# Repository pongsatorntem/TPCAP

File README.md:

TPCAP_autofeed_raspi --> can use in reality 100% detection at Export

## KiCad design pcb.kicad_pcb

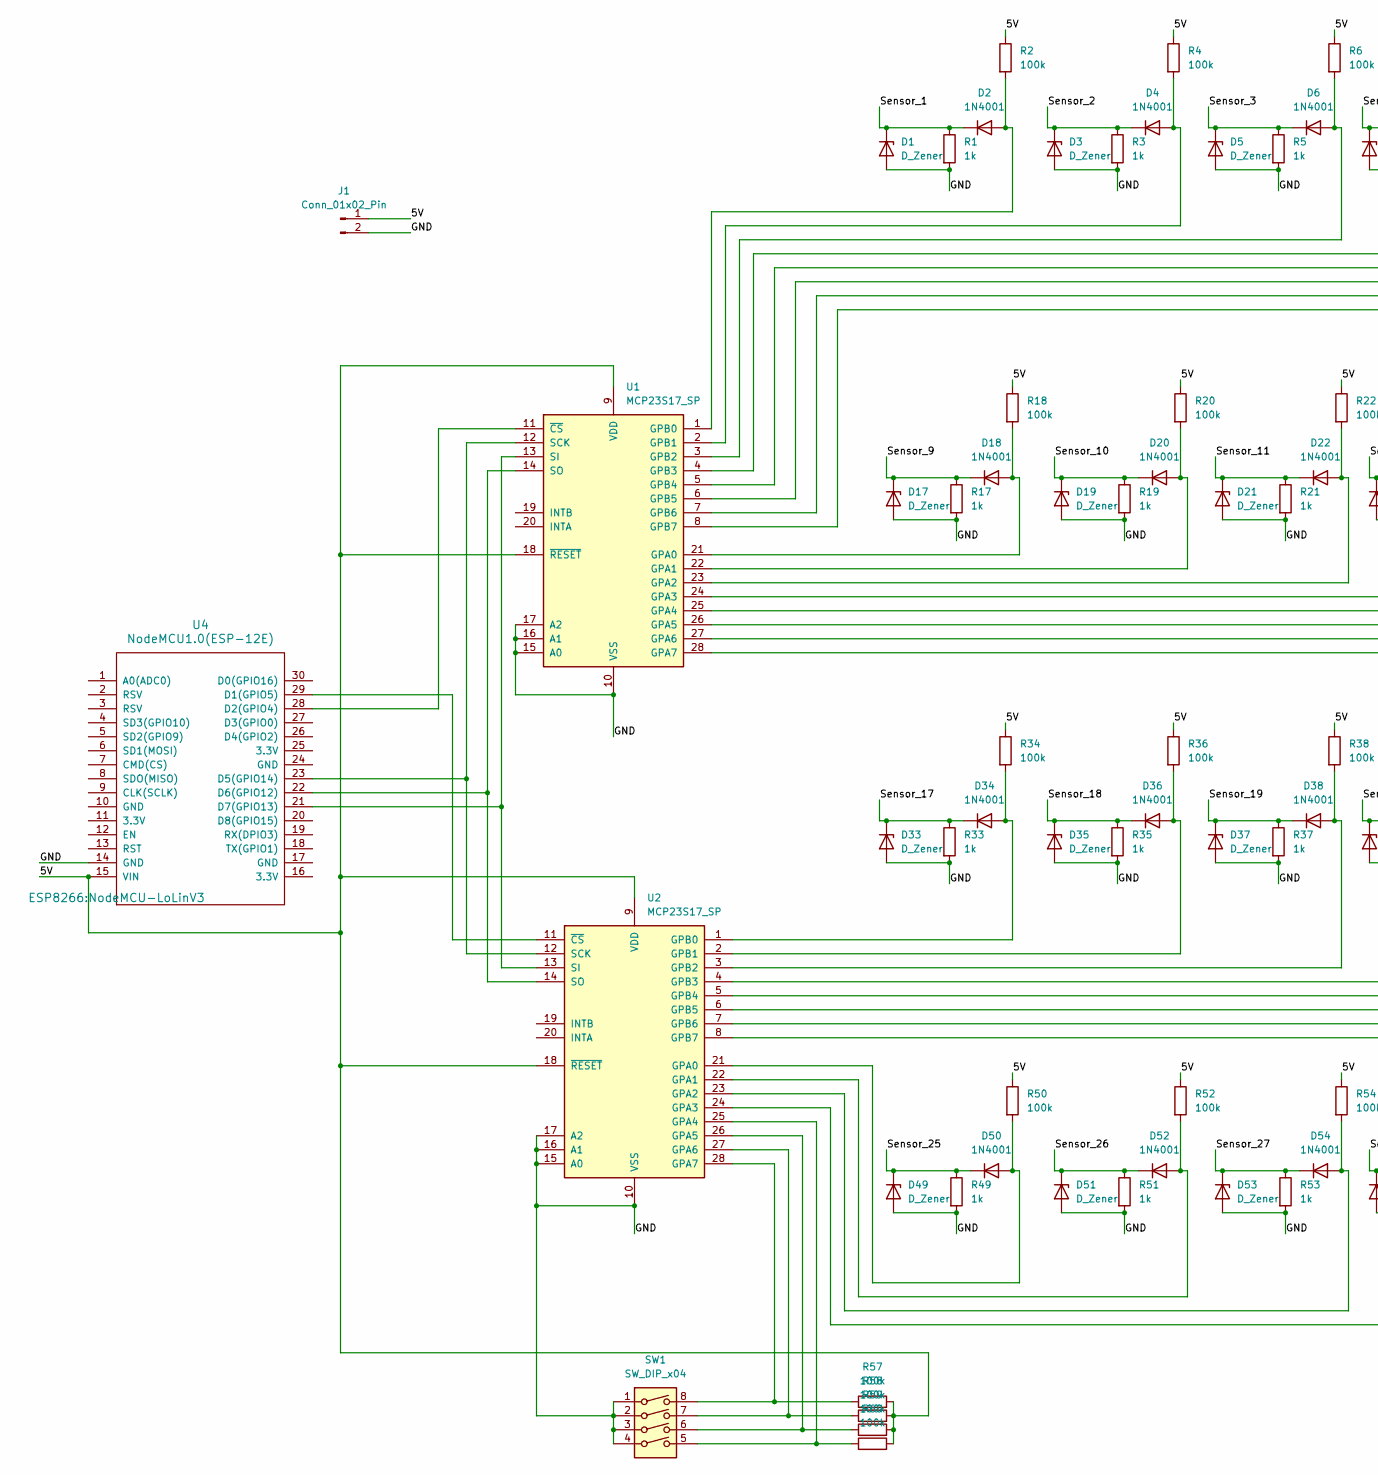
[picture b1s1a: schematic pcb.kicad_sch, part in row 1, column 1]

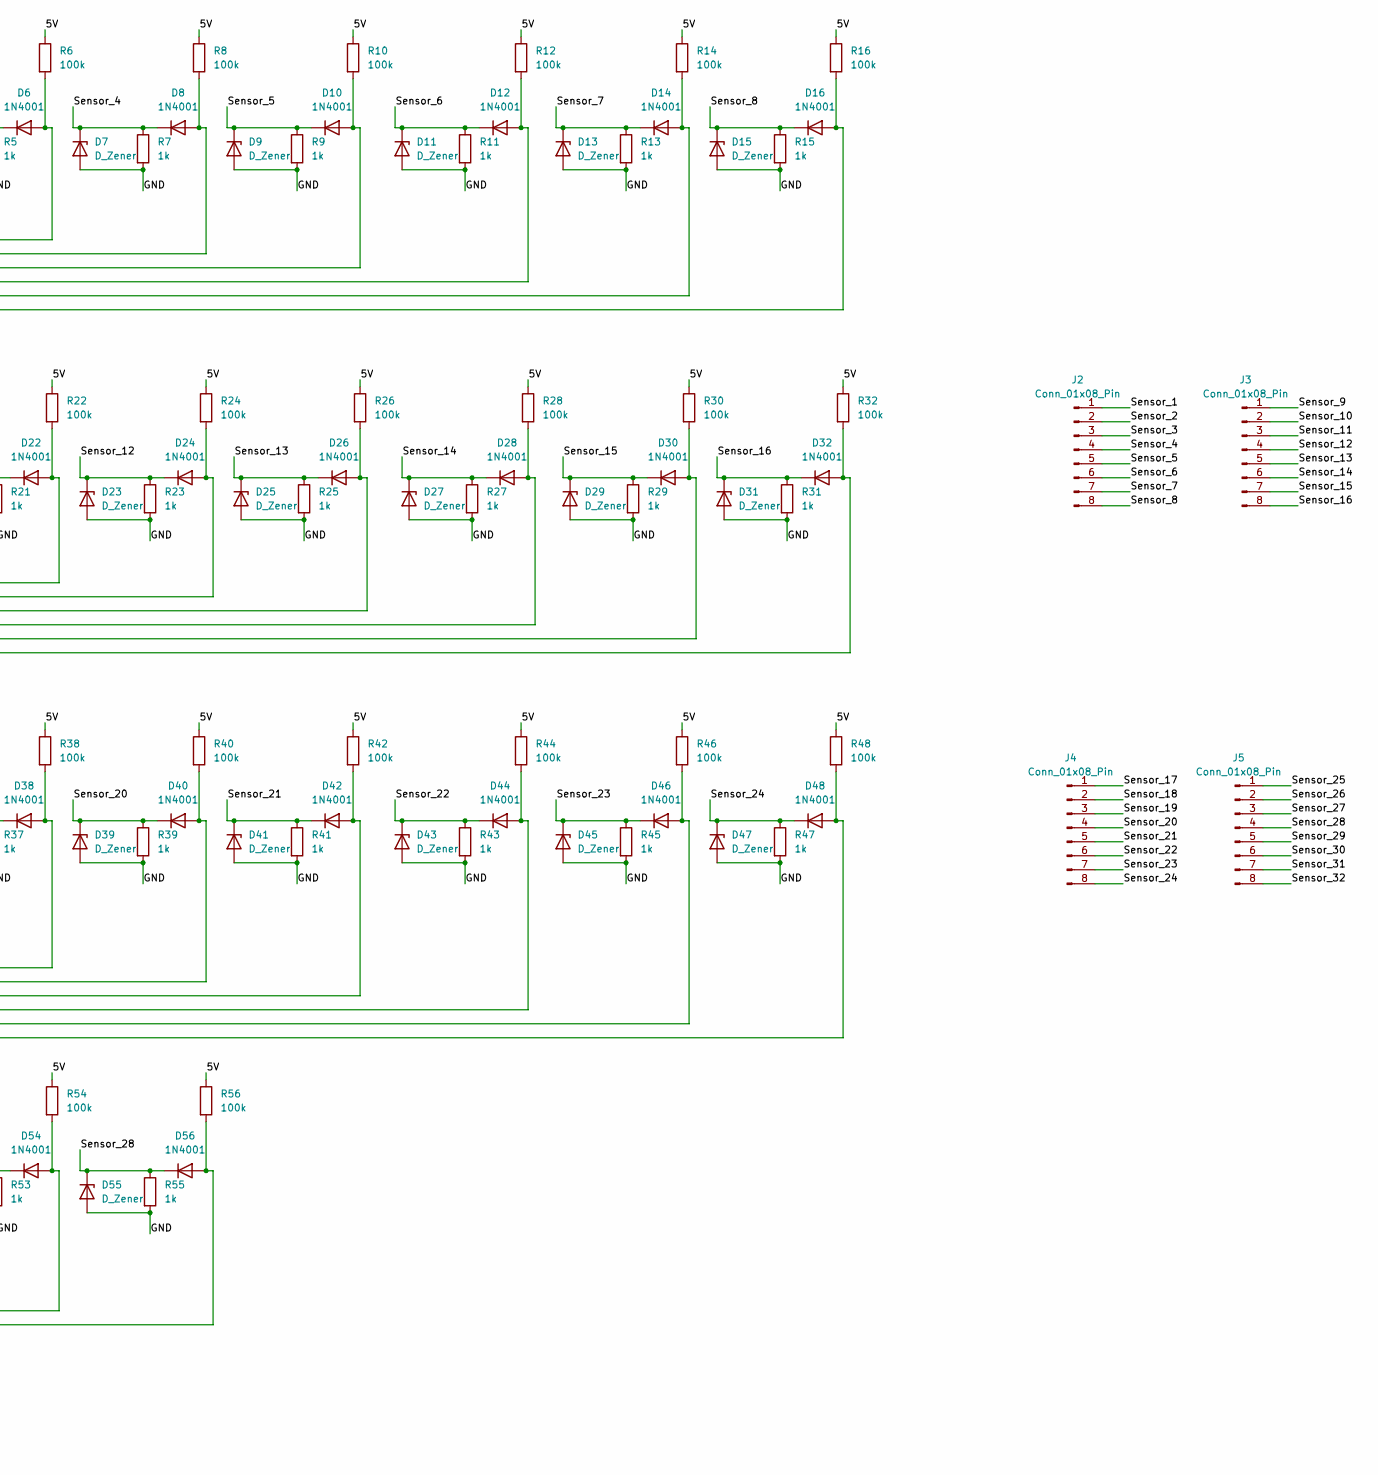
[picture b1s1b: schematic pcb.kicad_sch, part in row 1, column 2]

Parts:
D1, D3, D5, D7, D9, D11, D13, D15, D17, D19, D21, D23, D25, D27, D29, D31, D33, D35, D37, D39, D41, D43, D45, D47, D49, D51, D53, D55: D_Zener; D_DO-41_SOD81_P10.16mm_Horizontal
D2, D4, D6, D8, D10, D12, D14, D16, D18, D20, D22, D24, D26, D28, D30, D32, D34, D36, D38, D40, D42, D44, D46, D48, D50, D52, D54, D56: 1N4001; D_DO-41_SOD81_P10.16mm_Horizontal
J1: Conn_01x02_Pin; TerminalBlock_Phoenix_PT-1,5-2-3.5-H_1x02_P3.50mm_Horizontal
J2, J3, J4, J5: Conn_01x08_Pin; TerminalBlock_Phoenix_PT-1,5-8-3.5-H_1x08_P3.50mm_Horizontal
R1, R3, R5, R7, R9, R11, R13, R15, R17, R19, R21, R23, R25, R27, R29, R31, R33, R35, R37, R39, R41, R43, R45, R47, R49, R51, R53, R55: 1k; R_Axial_DIN0411_L9.9mm_D3.6mm_P12.70mm_Horizontal
R2, R4, R6, R8, R10, R12, R14, R16, R18, R20, R22, R24, R26, R28, R30, R32, R34, R36, R38, R40, R42, R44, R46, R48, R50, R52, R54, R56, R57, R58, R59, R60: 100k; R_Axial_DIN0411_L9.9mm_D3.6mm_P12.70mm_Horizontal
SW1: SW_DIP_x04; DIP-8_W7.62mm_Socket
U1, U2: MCP23S17_SP; DIP-28_W7.62mm
U4: NodeMCU1.0(ESP-12E); NodeMCU-LoLinV3

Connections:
/5V: J1.1, R2.1, R4.1, R6.1, R8.1, R10.1, R12.1, R14.1, R16.1, R18.1, R20.1, R22.1, R24.1, R26.1, R28.1, R30.1, R32.1, R34.1, R36.1, R38.1, R40.1, R42.1, R44.1, R46.1, R48.1, R50.1, R52.1, R54.1, R56.1, R57.2, R58.2, R59.2, R60.2, U1.9 (VDD), U1.18 (~RESET), U2.9 (VDD), U2.18 (~RESET), U4.15 (VIN)
/GND: D1.2 (A), D3.2 (A), D5.2 (A), D7.2 (A), D9.2 (A), D11.2 (A), D13.2 (A), D15.2 (A), D17.2 (A), D19.2 (A), D21.2 (A), D23.2 (A), D25.2 (A), D27.2 (A), D29.2 (A), D31.2 (A), D33.2 (A), D35.2 (A), D37.2 (A), D39.2 (A), D41.2 (A), D43.2 (A), D45.2 (A), D47.2 (A), D49.2 (A), D51.2 (A), D53.2 (A), D55.2 (A), J1.2, R1.2, R3.2, R5.2, R7.2, R9.2, R11.2, R13.2, R15.2, R17.2, R19.2, R21.2, R23.2, R25.2, R27.2, R29.2, R31.2, R33.2, R35.2, R37.2, R39.2, R41.2, R43.2, R45.2, R47.2, R49.2, R51.2, R53.2, R55.2, SW1.1, SW1.2, SW1.3, SW1.4, U1.10 (VSS), U1.15 (A0), U1.16 (A1), U1.17 (A2), U2.10 (VSS), U2.15 (A0), U2.16 (A1), U2.17 (A2), U4.14 (GND)
/Sensor_1: D1.1 (K), D2.1 (K), J2.1, R1.1
/Sensor_2: D3.1 (K), D4.1 (K), J2.2, R3.1
/Sensor_3: D5.1 (K), D6.1 (K), J2.3, R5.1
/Sensor_4: D7.1 (K), D8.1 (K), J2.4, R7.1
/Sensor_5: D9.1 (K), D10.1 (K), J2.5, R9.1
/Sensor_6: D11.1 (K), D12.1 (K), J2.6, R11.1
/Sensor_7: D13.1 (K), D14.1 (K), J2.7, R13.1
/Sensor_8: D15.1 (K), D16.1 (K), J2.8, R15.1
/Sensor_9: D17.1 (K), D18.1 (K), J3.1, R17.1
/Sensor_10: D19.1 (K), D20.1 (K), J3.2, R19.1
/Sensor_11: D21.1 (K), D22.1 (K), J3.3, R21.1
/Sensor_12: D23.1 (K), D24.1 (K), J3.4, R23.1
/Sensor_13: D25.1 (K), D26.1 (K), J3.5, R25.1
/Sensor_14: D27.1 (K), D28.1 (K), J3.6, R27.1
/Sensor_15: D29.1 (K), D30.1 (K), J3.7, R29.1
/Sensor_16: D31.1 (K), D32.1 (K), J3.8, R31.1
/Sensor_17: D33.1 (K), D34.1 (K), J4.1, R33.1
/Sensor_18: D35.1 (K), D36.1 (K), J4.2, R35.1
/Sensor_19: D37.1 (K), D38.1 (K), J4.3, R37.1
/Sensor_20: D39.1 (K), D40.1 (K), J4.4, R39.1
/Sensor_21: D41.1 (K), D42.1 (K), J4.5, R41.1
/Sensor_22: D43.1 (K), D44.1 (K), J4.6, R43.1
/Sensor_23: D45.1 (K), D46.1 (K), J4.7, R45.1
/Sensor_24: D47.1 (K), D48.1 (K), J4.8, R47.1
/Sensor_25: D49.1 (K), D50.1 (K), J5.1, R49.1
/Sensor_26: D51.1 (K), D52.1 (K), J5.2, R51.1
/Sensor_27: D53.1 (K), D54.1 (K), J5.3, R53.1
/Sensor_28: D55.1 (K), D56.1 (K), J5.4, R55.1
/Sensor_29: J5.5
/Sensor_30: J5.6
/Sensor_31: J5.7
/Sensor_32: J5.8
unnamed: D2.2 (A), R2.2, U1.1 (GPB0)
unnamed: D4.2 (A), R4.2, U1.2 (GPB1)
unnamed: D6.2 (A), R6.2, U1.3 (GPB2)
unnamed: D8.2 (A), R8.2, U1.4 (GPB3)
unnamed: D10.2 (A), R10.2, U1.5 (GPB4)
unnamed: D12.2 (A), R12.2, U1.6 (GPB5)
unnamed: D14.2 (A), R14.2, U1.7 (GPB6)
unnamed: D16.2 (A), R16.2, U1.8 (GPB7)
unnamed: D18.2 (A), R18.2, U1.21 (GPA0)
unnamed: D20.2 (A), R20.2, U1.22 (GPA1)
unnamed: D22.2 (A), R22.2, U1.23 (GPA2)
unnamed: D24.2 (A), R24.2, U1.24 (GPA3)
unnamed: D26.2 (A), R26.2, U1.25 (GPA4)
unnamed: D28.2 (A), R28.2, U1.26 (GPA5)
unnamed: D30.2 (A), R30.2, U1.27 (GPA6)
unnamed: D32.2 (A), R32.2, U1.28 (GPA7)
unnamed: D34.2 (A), R34.2, U2.1 (GPB0)
unnamed: D36.2 (A), R36.2, U2.2 (GPB1)
unnamed: D38.2 (A), R38.2, U2.3 (GPB2)
unnamed: D40.2 (A), R40.2, U2.4 (GPB3)
unnamed: D42.2 (A), R42.2, U2.5 (GPB4)
unnamed: D44.2 (A), R44.2, U2.6 (GPB5)
unnamed: D46.2 (A), R46.2, U2.7 (GPB6)
unnamed: D48.2 (A), R48.2, U2.8 (GPB7)
unnamed: D50.2 (A), R50.2, U2.21 (GPA0)
unnamed: D52.2 (A), R52.2, U2.22 (GPA1)
unnamed: D54.2 (A), R54.2, U2.23 (GPA2)
unnamed: D56.2 (A), R56.2, U2.24 (GPA3)
unnamed: U1.12 (SCK), U2.12 (SCK), U4.23 (D5(GPIO14))
unnamed: U1.13 (SI), U2.13 (SI), U4.21 (D7(GPIO13))
unnamed: U1.14 (SO), U2.14 (SO), U4.22 (D6(GPIO12))
unnamed: U1.11 (~CS), U4.28 (D2(GPIO4))
unnamed: R60.1, SW1.5, U2.25 (GPA4)
unnamed: R59.1, SW1.6, U2.26 (GPA5)
unnamed: R58.1, SW1.7, U2.27 (GPA6)
unnamed: R57.1, SW1.8, U2.28 (GPA7)
unnamed: U2.11 (~CS), U4.29 (D1(GPIO5))

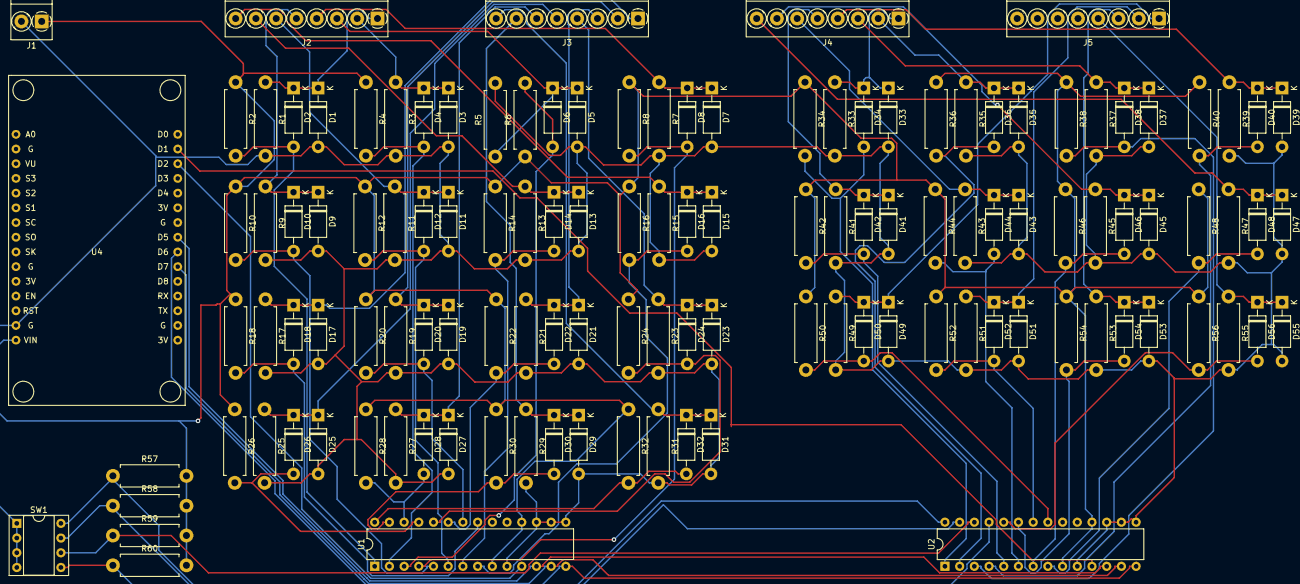
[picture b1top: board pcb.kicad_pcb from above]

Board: 2 copper layers, 125 parts (0 on the bottom side), 67 nets.

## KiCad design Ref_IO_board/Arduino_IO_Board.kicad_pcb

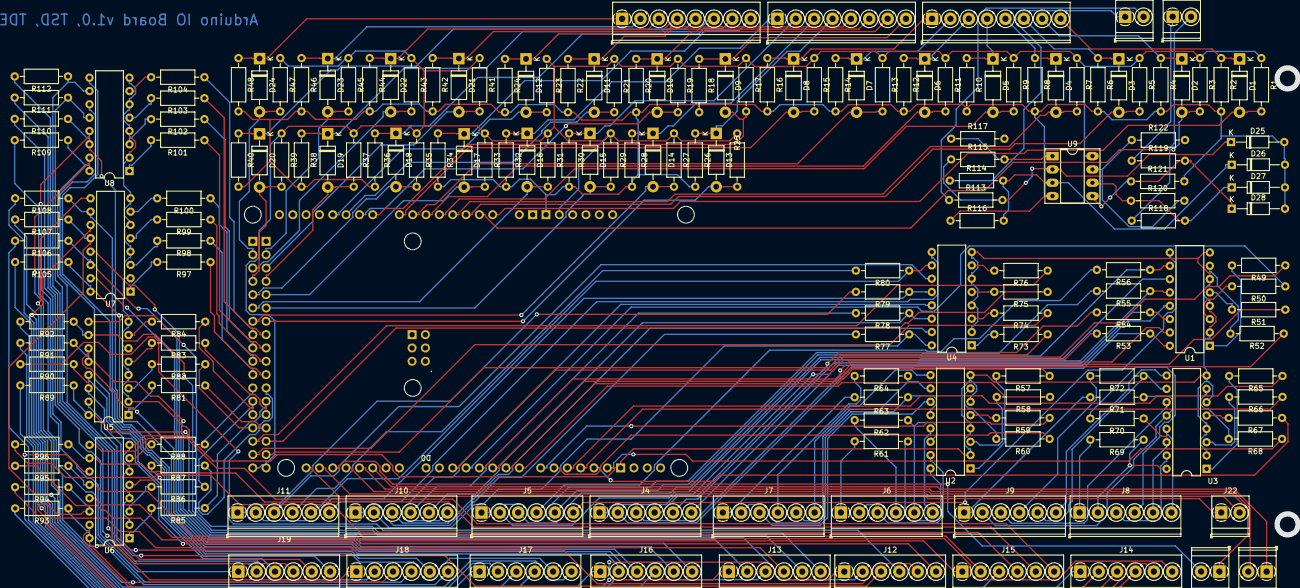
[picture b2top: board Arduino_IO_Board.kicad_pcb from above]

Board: 2 copper layers, 184 parts (0 on the bottom side), 227 nets.

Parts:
A1: Arduino_Mega2560_R3_Shield
D1, D2, D3, D4, D5, D6, D7, D8, D9, D10, D11, D12, D13, D14, D15, D16, D17, D18, D19, D20, D21, D22, D23, D24: 1N4002; D_DO-41_SOD81_P10.16mm_Horizontal
D25, D26, D27, D28: 1N53xxB; D_DO-35_SOD27_P10.16mm_Horizontal
J1, J2, J3: Screw_Terminal_01x08; TerminalBlock_Phoenix_PT-1,5-8-3.5-H_1x08_P3.50mm_Horizontal
J4, J5, J6, J7, J8, J9, J10, J11, J12, J13, J14, J15, J16, J17, J18, J19: Screw_Terminal_01x06; TerminalBlock_Phoenix_PT-1,5-6-3.5-H_1x06_P3.50mm_Horizontal
J20, J21, J22, J23, J24: Screw_Terminal_01x02; TerminalBlock_Phoenix_PT-1,5-2-3.5-H_1x02_P3.50mm_Horizontal
R1, R3, R5, R7, R9, R11, R13, R15, R17, R19, R21, R23, R25, R27, R29, R31, R33, R35, R37, R39, R41, R43, R45, R47: 5.1k; R_Axial_DIN0207_L6.3mm_D2.5mm_P10.16mm_Horizontal
R2, R4, R6, R8, R10, R12, R14, R16, R18, R20, R22, R24, R26, R28, R30, R32, R34, R36, R38, R40, R42, R44, R46, R48: 100k; R_Axial_DIN0207_L6.3mm_D2.5mm_P10.16mm_Horizontal
R49, R50, R51, R52, R57, R58, R59, R60, R65, R66, R67, R68, R73, R74, R75, R76, R81, R82, R83, R84, R85, R86, R87, R88, R97, R98, R99, R100, R101, R102, R103, R104: 240; R_Axial_DIN0207_L6.3mm_D2.5mm_P10.16mm_Horizontal
R53, R54, R55, R56, R61, R62, R63, R64, R69, R70, R71, R72, R77, R78, R79, R80, R89, R90, R91, R92, R93, R94, R95, R96, R105, R106, R107, R108, R109, R110, R111, R112: 10k; R_Axial_DIN0207_L6.3mm_D2.5mm_P10.16mm_Horizontal
R113, R114, R115, R116, R118, R119, R120, R121: 200k; R_Axial_DIN0207_L6.3mm_D2.5mm_P10.16mm_Horizontal
R117, R122: 100; R_Axial_DIN0207_L6.3mm_D2.5mm_P10.16mm_Horizontal
U1, U2, U3, U4, U5, U6, U7, U8: LTV-847; DIP-16_W7.62mm
U9: TLC272; DIP-8_W7.62mm_Socket_LongPads

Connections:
+5V: A1.5V1 (5V), A1.5V3 (5V), A1.5V4 (5V), R1.1, R3.1, R5.1, R7.1, R9.1, R11.1, R13.1, R15.1, R17.1, R19.1, R21.1, R23.1, R25.1, R27.1, R29.1, R31.1, R33.1, R35.1, R37.1, R39.1, R41.1, R43.1, R45.1, R47.1, U9.8 (V+)
/A0: A1.A0, D1.2 (A), R1.2
/A1: A1.A1, D2.2 (A), R3.2
/A2: A1.A2, D3.2 (A), R5.2
/A3: A1.A3, D4.2 (A), R7.2
/A4: A1.A4, D5.2 (A), R9.2
/A5: A1.A5, D6.2 (A), R11.2
/A6: A1.A6, D7.2 (A), R13.2
/A7: A1.A7, D8.2 (A), R15.2
/A8: A1.A8, D9.2 (A), R17.2
/A9: A1.A9, D10.2 (A), R19.2
/A10: A1.A10, D11.2 (A), R21.2
/A11: A1.A11, D12.2 (A), R23.2
/D2: A1.D2 (D2_INT0), R49.1
/D3: A1.D3 (D3_INT1), R50.1
/D4: A1.D4, R51.1
/D5: A1.D5, R52.1
/D6: A1.D6, R57.1
/D7: A1.D7, R58.1
/D8: A1.D8, R59.1
/D9: A1.D9, R60.1
/D10: A1.D10, R65.1
/D11: A1.D11, R66.1
/D12: A1.D12, R67.1
/D13: A1.D13, R68.1
/D22: A1.D22, R73.1
/D23: A1.D23, R74.1
/D24: A1.D24, R75.1
/D25: A1.D25, R76.1
/D26: A1.D26, R81.1
/D27: A1.D27, R82.1
/D28: A1.D28, R83.1
/D29: A1.D29, R84.1
/D30: A1.D30, R85.1
/D31: A1.D31, R86.1
/D32: A1.D32, R87.1
/D33: A1.D33, R88.1
/D34: A1.D34, R97.1
/D35: A1.D35, R98.1
/D36: A1.D36, R99.1
/D37: A1.D37, R100.1
/D38: A1.D38, R101.1
/D39: A1.D39, R102.1
/D40: A1.D40, R103.1
/D41: A1.D41, R104.1
/D42: A1.D42, D13.2 (A), R25.2
/D43: A1.D43, D14.2 (A), R27.2
/D44: A1.D44, D15.2 (A), R29.2
/D45: A1.D45, D16.2 (A), R31.2
/D46: A1.D46, D17.2 (A), R33.2
/D47: A1.D47, D18.2 (A), R35.2
/D48: A1.D48, D19.2 (A), R37.2
/D49: A1.D49, D20.2 (A), R39.2
/D50: A1.D50 (D50_MISO), D21.2 (A), R41.2
/D51: A1.D51 (D51_MOSI), D22.2 (A), R43.2
/D52: A1.D52 (D52_SCK), D23.2 (A), R45.2
/D53: A1.D53 (D53_CS), D24.2 (A), R47.2
GND: A1.GND1 (GND), U1.2, U1.4, U1.6, U1.8, U2.2, U2.4, U2.6, U2.8, U3.2, U3.4, U3.6, U3.8, U4.2, U4.4, U4.6, U4.8, U5.2, U5.4, U5.6, U5.8, U6.2, U6.4, U6.6, U6.8, U7.2, U7.4, U7.6, U7.8, U8.2, U8.4, U8.6, U8.8
GND1: A1.GND2 (GND), D25.2 (A), D26.2 (A), D27.2 (A), D28.2 (A), R2.2, R4.2, R6.2, R8.2, R10.2, R12.2, R14.2, R16.2, R18.2, R20.2, R22.2, R24.2, R26.2, R28.2, R30.2, R32.2, R34.2, R36.2, R38.2, R40.2, R42.2, R44.2, R46.2, R48.2, R116.1, R121.2, U9.4 (V-)
unnamed: A1.D16 (D16/TX2), J21.1
unnamed: A1.D17 (D17/RX2), J21.2
unnamed: A1.D18 (D18/TX1), J20.1
unnamed: A1.D19 (D19/RX1), J20.2
unnamed: A1.D20 (D20/SDA), J22.2
unnamed: A1.D21 (D21/SCL), J22.1
unnamed: D1.1 (K), J1.8, R2.1
unnamed: D2.1 (K), J1.7, R4.1
unnamed: D3.1 (K), J1.6, R6.1
unnamed: D4.1 (K), J1.5, R8.1
unnamed: D5.1 (K), J1.4, R10.1
unnamed: D6.1 (K), J1.3, R12.1
unnamed: D7.1 (K), J1.2, R14.1
unnamed: D8.1 (K), J1.1, R16.1
unnamed: D9.1 (K), J2.8, R18.1
unnamed: D10.1 (K), J2.7, R20.1
unnamed: D11.1 (K), J2.6, R22.1
unnamed: D12.1 (K), J2.5, R24.1
unnamed: D13.1 (K), J2.4, R26.1
unnamed: D14.1 (K), J2.3, R28.1
unnamed: D15.1 (K), J2.2, R30.1
unnamed: D16.1 (K), J2.1, R32.1
unnamed: D17.1 (K), J3.8, R34.1
unnamed: D18.1 (K), J3.7, R36.1
unnamed: D19.1 (K), J3.6, R38.1
unnamed: D20.1 (K), J3.5, R40.1
unnamed: D21.1 (K), J3.4, R42.1
unnamed: D22.1 (K), J3.3, R44.1
unnamed: D23.1 (K), J3.2, R46.1
unnamed: D24.1 (K), J3.1, R48.1
unnamed: D25.1 (K), R113.2, R115.1, U9.2 (-)
unnamed: D26.1 (K), R114.2, R116.2, U9.3 (+)
unnamed: D27.1 (K), R118.2, R120.1, U9.6 (-)
unnamed: D28.1 (K), R119.2, R121.1, U9.5 (+)
unnamed: J4.1, R53.2
unnamed: J4.2, R53.1, U1.16
unnamed: J4.3, U1.15
unnamed: J4.4, R54.2
unnamed: J4.5, R54.1, U1.14
unnamed: J4.6, U1.13
unnamed: J5.1, R55.2
unnamed: J5.2, R55.1, U1.12
unnamed: J5.3, U1.11
unnamed: J5.4, R56.2
unnamed: J5.5, R56.1, U1.10
unnamed: J5.6, U1.9
unnamed: J6.1, R61.2
unnamed: J6.2, R61.1, U2.16
unnamed: J6.3, U2.15
unnamed: J6.4, R62.2
unnamed: J6.5, R62.1, U2.14
unnamed: J6.6, U2.13
unnamed: J7.1, R63.2
unnamed: J7.2, R63.1, U2.12
unnamed: J7.3, U2.11
unnamed: J7.4, R64.2
unnamed: J7.5, R64.1, U2.10
unnamed: J7.6, U2.9
unnamed: J8.1, R69.2
unnamed: J8.2, R69.1, U3.16
unnamed: J8.3, U3.15
unnamed: J8.4, R70.2
unnamed: J8.5, R70.1, U3.14
unnamed: J8.6, U3.13
unnamed: J9.1, R71.2
unnamed: J9.2, R71.1, U3.12
unnamed: J9.3, U3.11
unnamed: J9.4, R72.2
unnamed: J9.5, R72.1, U3.10
unnamed: J9.6, U3.9
unnamed: J10.1, R77.2
unnamed: J10.2, R77.1, U4.16
unnamed: J10.3, U4.15
unnamed: J10.4, R78.2
unnamed: J10.5, R78.1, U4.14
unnamed: J10.6, U4.13
unnamed: J11.1, R79.2
unnamed: J11.2, R79.1, U4.12
unnamed: J11.3, U4.11
unnamed: J11.4, R80.2
unnamed: J11.5, R80.1, U4.10
unnamed: J11.6, U4.9
unnamed: J12.1, R89.2
unnamed: J12.2, R89.1, U5.16
unnamed: J12.3, U5.15
unnamed: J12.4, R90.2
unnamed: J12.5, R90.1, U5.14
unnamed: J12.6, U5.13
unnamed: J13.1, R91.2
unnamed: J13.2, R91.1, U5.12
unnamed: J13.3, U5.11
unnamed: J13.4, R92.2
unnamed: J13.5, R92.1, U5.10
unnamed: J13.6, U5.9
unnamed: J14.1, R93.2
unnamed: J14.2, R93.1, U6.16
unnamed: J14.3, U6.15
unnamed: J14.4, R94.2
unnamed: J14.5, R94.1, U6.14
unnamed: J14.6, U6.13
unnamed: J15.1, R95.2
unnamed: J15.2, R95.1, U6.12
unnamed: J15.3, U6.11
unnamed: J15.4, R96.2
unnamed: J15.5, R96.1, U6.10
unnamed: J15.6, U6.9
unnamed: J16.1, R105.2
unnamed: J16.2, R105.1, U7.16
unnamed: J16.3, U7.15
unnamed: J16.4, R106.2
unnamed: J16.5, R106.1, U7.14
unnamed: J16.6, U7.13
unnamed: J17.1, R107.2
unnamed: J17.2, R107.1, U7.12
unnamed: J17.3, U7.11
unnamed: J17.4, R108.2
unnamed: J17.5, R108.1, U7.10
unnamed: J17.6, U7.9
unnamed: J18.1, R109.2
unnamed: J18.2, R109.1, U8.16
unnamed: J18.3, U8.15
unnamed: J18.4, R110.2
unnamed: J18.5, R110.1, U8.14
unnamed: J18.6, U8.13
unnamed: J19.1, R111.2
unnamed: J19.2, R111.1, U8.12
unnamed: J19.3, U8.11
unnamed: J19.4, R112.2
unnamed: J19.5, R112.1, U8.10
unnamed: J19.6, U8.9
unnamed: J23.1, R114.1
unnamed: J23.2, R113.1
unnamed: J24.1, R119.1
unnamed: J24.2, R118.1
unnamed: R49.2, U1.1
unnamed: R50.2, U1.3
unnamed: R51.2, U1.5
unnamed: R52.2, U1.7
unnamed: R57.2, U2.1
unnamed: R58.2, U2.3
unnamed: R59.2, U2.5
unnamed: R60.2, U2.7
unnamed: R65.2, U3.1
unnamed: R66.2, U3.3
unnamed: R67.2, U3.5
unnamed: R68.2, U3.7
unnamed: R73.2, U4.1
unnamed: R74.2, U4.3
unnamed: R75.2, U4.5
unnamed: R76.2, U4.7
unnamed: R81.2, U5.1
unnamed: R82.2, U5.3
unnamed: R83.2, U5.5
unnamed: R84.2, U5.7
unnamed: R85.2, U6.1
unnamed: R86.2, U6.3
unnamed: R87.2, U6.5
unnamed: R88.2, U6.7
unnamed: R97.2, U7.1
unnamed: R98.2, U7.3
unnamed: R99.2, U7.5
unnamed: R100.2, U7.7
unnamed: R101.2, U8.1
unnamed: R102.2, U8.3
unnamed: R103.2, U8.5
unnamed: R104.2, U8.7
unnamed: R115.2, R117.1, U9.1
unnamed: R120.2, R122.1, U9.7

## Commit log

2024-09-13 Already Test
2024-09-13 Already test at SVA 13 Sept (Demo flowrack)
2024-09-13 test for new file
2024-09-26 can read photo from get
2025-03-18 no hold flag Full in recieve_flowrack type
2025-03-18 // FULL can release flag
2025-03-19 ใส่โค้ดแก้ full เพิ่ม ยังไม่เรียลทา ต้อเชคใน loop
2025-03-19 has a debug for wifi
2025-03-19 checkFULLrealtimefollowGPT
2025-03-20 comment the queue ไว้ เพราะตอบสนองช้า
2025-03-20 handle with FULL noFULL but not open retryrequest
2025-03-24 add wake up MCP and debug wifi more remain cout up
2025-03-27 add flag to HOLD
2025-03-31 90% ใช้งานได้ แค่มีรีเซ็ตตัวเองบ้าง //ก่อนจะเชค F
2025-03-31 ชิฟเวลารีเควส ป้องกันส่งซ้ำๆเหมือนnoise วนลูป Fu
2025-04-04 เสถียรละ ขาดแค่รอ server 200
2025-04-08 แก้ ip ตรง localIP ละได้เลย
2025-04-22 สแกนหา wifi แข็งแรงสุด ลด heap เพื่อ HP2+bin
2025-04-22 สแกนหา wifi str แต่ยังไม่ได้ลด heap ใช้hp3-4ได้
2025-04-22 แก้เรื่องของการเกิด fragment HEAP มีปัญหาปกติ47%ละ
2025-04-22 แก้เรื่อง fragment HEAP ปกติ 47% ละ มีprintโชตลอด
2025-05-07 HP3-6
2025-05-07 น่าจะเป็นoriginalที่หาเจอสุดๆละไม่มีตั้งเวลารีเซ็ต
2025-05-07 ลดprint log ลงมีเพิ่มรีเซ็ต 6.00 12.00
2025-05-07 test at HP4 โค้ด original + reset 6,12
2025-05-08 count_up ถูก แค่ full ค้างเวลากล่องผ่าน
2025-05-08 ใช้อันนี้กับ hp2 ไปก่อน พอได้อยู่ แค่รีเซ็ตบ่อ8May
2025-05-25 เวอชั่นต๊ะ ใส่functionท้อปเพิ่มเข้าไป
2025-07-02 lidar config
2025-07-19 update interpolation method more eff
2025-09-21 for test on Monday 22Sep25
2025-09-21 test on Monday 22Sep25
2025-09-21 for test 22Sep25
2025-09-29 Raspi (Can use at Export)
